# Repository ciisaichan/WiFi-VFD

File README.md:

# WiFi-VFD
开源的ESP8266驱动VFD屏电路，支持BiliBili粉丝数、时间、温度、湿度

### 视频
<https://www.bilibili.com/video/BV1Lp4y1t7u1>

### 目录/文件介绍
- firmware : 固件源代码文件
    - for_ArduinoIDE : ArduinoIDE 格式
    - for_PlatformIO : PlatformIO 格式
    - Description_CN.pdf : 配网以及功能的说明书
    - VFD_datasheet.pdf : VFD模块数据表
- hardware : 电路设计工程文件（KiCad格式）
    - gerber : PCB生产文件
    - wifivfd.pro : KiCad工程
    - wifivfd.kicad_pcb : PCB设计
    - wifivfd.sch : 电路设计
    - BOM_CN.csv : 零件配单表（中文）
    - BOM_EN.csv : 零件配单表（English）

### 成品图

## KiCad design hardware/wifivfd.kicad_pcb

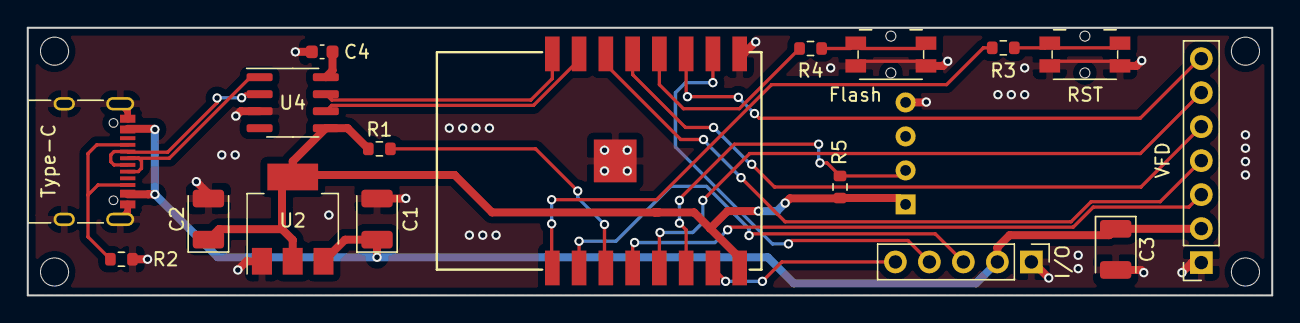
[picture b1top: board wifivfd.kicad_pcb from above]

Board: 2 copper layers, 93.0 x 20.0 mm, 18 parts (1 on the bottom side), 23 nets.

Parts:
C1, C2, C3: 10uF; CP_EIA-3528-21_Kemet-B
C4: 100nF; C_0603_1608Metric
DHT11: DHT11; Aosong_DHT11_5.5x12.0_P2.54mm
Flash: KEY_Flash; Panasonic_EVQPUL_EVQPUC
I/O: Conn_OutPin; PinHeader_1x05_P2.54mm_Vertical
R1, R3, R4: 470; R_0603_1608Metric
R2, R5: 4.7k; R_0603_1608Metric
RST: KEY_RST; Panasonic_EVQPUL_EVQPUC
Type-C: USB_C_Receptacle_USB2.0; USB_C_Receptacle_XKB_U262-16XN-4BVC11
U1: ESP-12S
U2: NCP1117-3.3_SOT223; SOT-223-3_TabPin2
U4: CH330N; SOIC-8_3.9x4.9mm_P1.27mm
VFD: Conn_VFD; PinSocket_1x07_P2.54mm_Vertical

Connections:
+3V3: C2.1, DHT11.1, R1.2, R5.2, U1.8, U2.2, U4.5
+5V: C1.1, C3.1, I/O.2, Type-C.A4, Type-C.A9, Type-C.B4, Type-C.B9, U2.3, VFD.2
/ADC: I/O.3, U1.2
/D_N: Type-C.A7, Type-C.B7, U4.2
/D_P: Type-C.A6, Type-C.B6, U4.1
/GPIO0: R4.1, U1.12
/PIN_D0: U1.4, VFD.3
/PIN_D1: U1.14, VFD.4
/PIN_D2: U1.13, VFD.5
/PIN_D4: U1.11, VFD.7
/PIN_D5: U1.5, VFD.6
/PIN_D6: DHT11.2, R5.1, U1.6
/PIN_D7: I/O.5, U1.7
/PIN_D8: I/O.4, U1.10
/RXD0: U1.15, U4.6
/TXD0: U1.16, U4.7
/nRST: R3.1, U1.1
GND: C1.2, C2.2, C3.2, C4.2, DHT11.4, Flash.2, I/O.1, R2.1, RST.2, Type-C.A1, Type-C.A12, Type-C.B1, Type-C.B12, Type-C.S1, U1.9, U1.P$1, U2.1, U4.3, VFD.1
unnamed: C4.1, U4.8
unnamed: R2.2, Type-C.A5, Type-C.B5
unnamed: R1.1, U1.3
unnamed: R3.2, RST.1
unnamed: Flash.1, R4.2

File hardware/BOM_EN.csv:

Comment,Description,Designator,Footprint,Pins,Quantity,
10uF,desc,"C3,C2,C1,",CP_EIA-3528-21_Kemet-B,2,3,
100nF,desc,"C4,",C_0603_1608Metric,2,1,
470¦¸,desc,"R4,R3,R1,",R_0603_1608Metric,2,3,
4.7k,desc,"R5,R2,",R_0603_1608Metric,2,2,
ESP-12S,desc,"U1,",ESP-12S,17,1,
NCP1117-3.3_SOT223,desc,"U2,",SOT-223-3_TabPin2,4,1,
CH330N,desc,"U4,",SOIC-8_3.9x4.9mm_P1.27mm,8,1,
KEY_Flash,desc,"Flash,",Panasonic_EVQPUL_EVQPUC,6,1,
KEY_RST,desc,"RST,",Panasonic_EVQPUL_EVQPUC,6,1,
USB_C_Receptacle_USB2.0,desc,"Type-C,",USB_C_Receptacle_XKB_U262-16XN-4BVC11,22,1,
Conn_VFD,desc,"VFD,",PinSocket_1x07_P2.54mm_Vertical,7,1,
DHT11,desc,"DHT11,",Aosong_DHT11_5.5x12.0_P2.54mm,4,1,
,,,,,,
VFD module,8-MD-06INKM,,,7,1,https://item.taobao.com/item.htm?id=597649622906
Lengthening nut,M2x12mm,,,,4,
Screws,M2x6mm,,,,8,

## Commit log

2021-05-12 upload
2021-05-12 Create LICENSE
